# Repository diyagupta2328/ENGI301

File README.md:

# ENGI301
Repository for ENGI301 Coursework!

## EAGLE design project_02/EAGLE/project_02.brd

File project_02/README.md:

# Sign Talk PCB
This project is a PCB designed for Project 1 from this class. The updated system block diagram and a mechanical drawing is in a ppt in the project_02 folder. Through this project I was introduced to Eagle for designing and PCB and went through the process of getting a PCB ready for manufacture. 

This repository includes a schematic as a pdf, all the EAGLE files (library, schematic, board), manufacturing files, and implementation files.

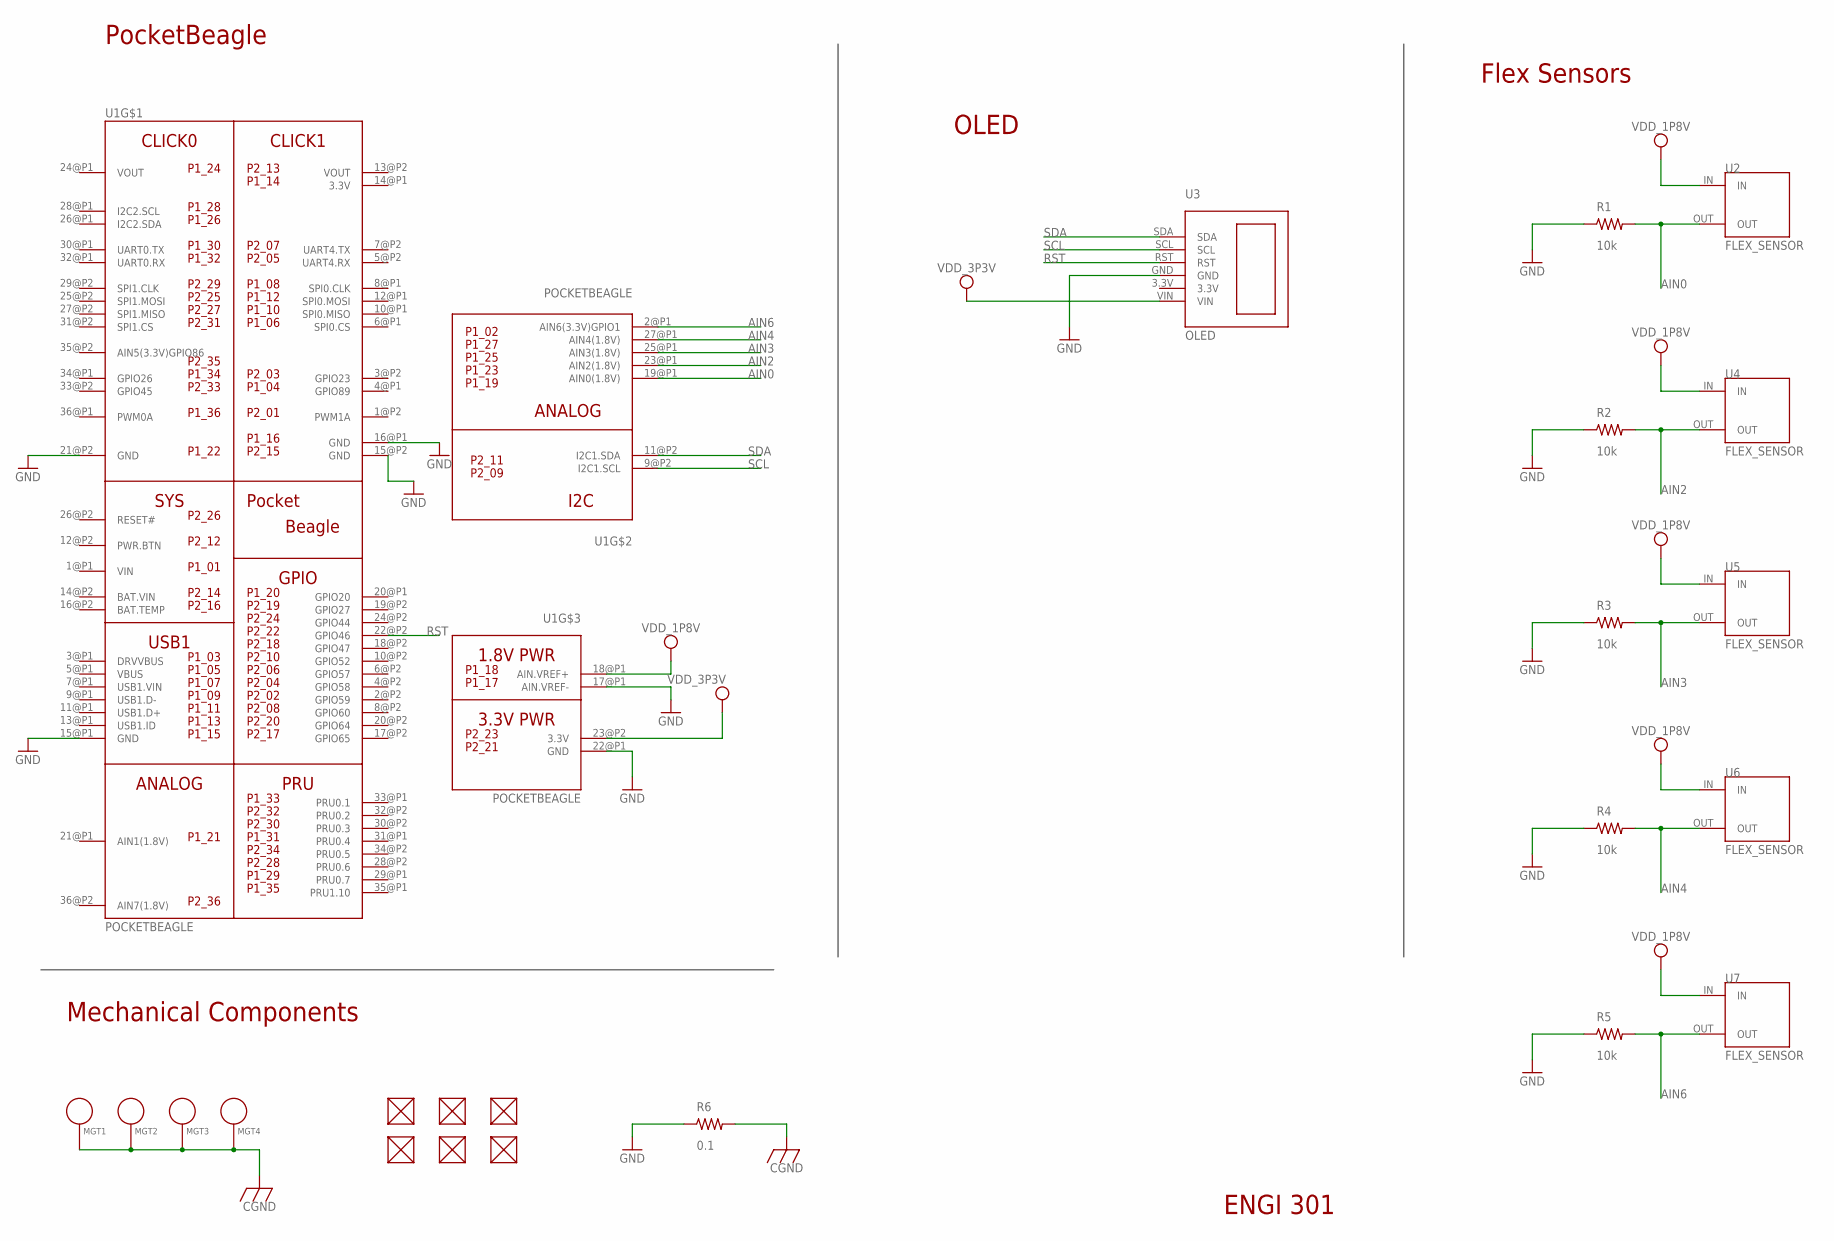
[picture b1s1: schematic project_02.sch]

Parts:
FUD1, FUD2, FUD3, FUD4, FUD5, FUD6: FIDUCIAL; FIDUCIAL_40MIL
MGT1, MGT2, MGT3, MGT4: MOUNTING_HOLE
R1, R2, R3, R4, R5: 10k; R0603
R6: 0.1; R0603
U1: POCKETBEAGLE
U2, U4, U5, U6, U7: FLEX_SENSOR
U3: OLED

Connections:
3.3V: U1.14@P1 (3.3V)
AIN0: R1.2, U1.19@P1 (AIN0(1.8V)), U2.OUT
AIN2: R2.2, U1.23@P1 (AIN2(1.8V)), U4.OUT
AIN3: R3.2, U1.25@P1 (AIN3(1.8V)), U5.OUT
AIN4: R4.2, U1.27@P1 (AIN4(1.8V)), U6.OUT
AIN6: R5.2, U1.2@P1 (AIN6(3.3V)GPIO1), U7.OUT
BAT.VIN: U1.14@P2 (BAT.VIN)
CGND: MGT1.P$1, MGT2.P$1, MGT3.P$1, MGT4.P$1, R6.2
GND: R1.1, R2.1, R3.1, R4.1, R5.1, R6.1, U1.15@P1 (GND), U1.15@P2 (GND), U1.16@P1 (GND), U1.17@P1 (AIN.VREF-), U1.21@P2 (GND), U1.22@P1 (GND), U3.GND
RST: U1.22@P2 (GPIO46), U3.RST
SCL: U1.9@P2 (I2C1.SCL), U3.SCL
SDA: U1.11@P2 (I2C1.SDA), U3.SDA
VDD_1P8V: U1.18@P1 (AIN.VREF+), U2.IN, U4.IN, U5.IN, U6.IN, U7.IN
VDD_3P3V: U1.23@P2 (3.3V), U3.VIN
VIN: U1.1@P1 (VIN)
VOUT: U1.13@P2 (VOUT), U1.24@P1 (VOUT)

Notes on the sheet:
Mechanical Components
PocketBeagle
OLED
Flex Sensors
ENGI 301

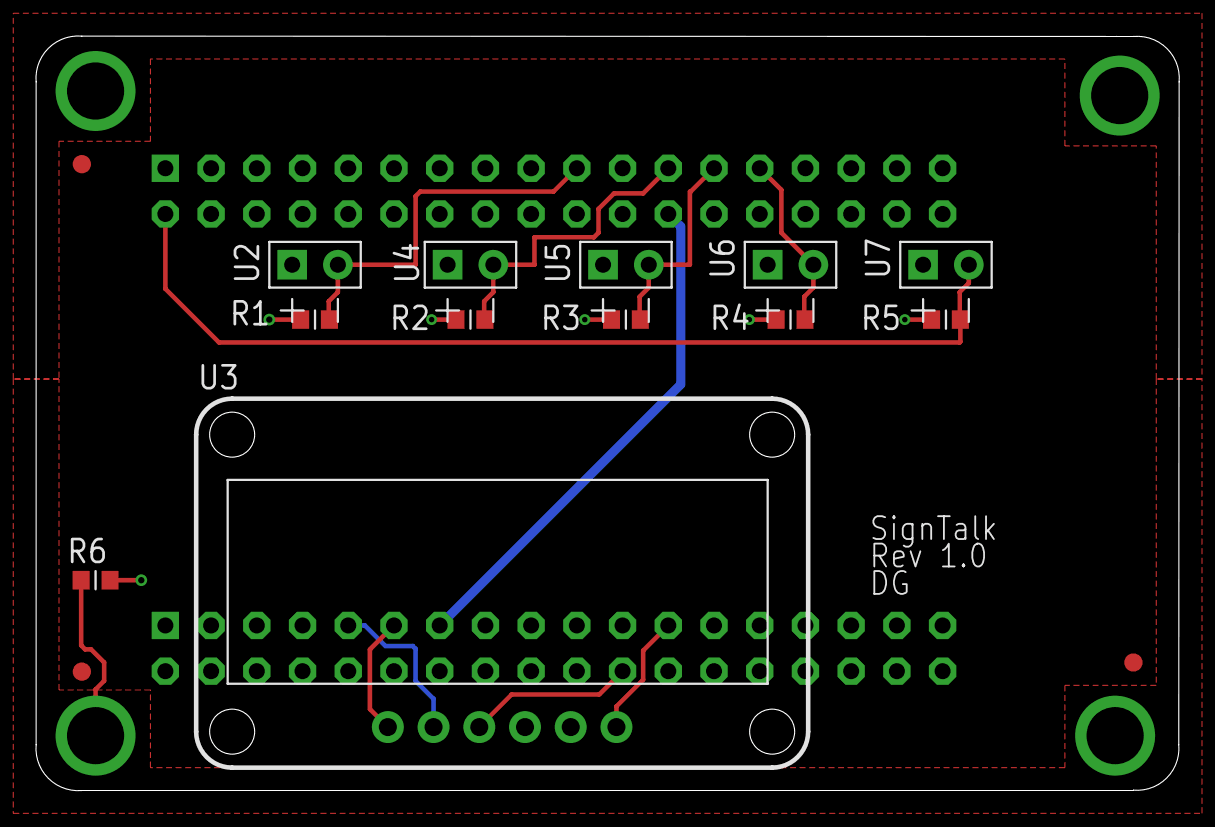
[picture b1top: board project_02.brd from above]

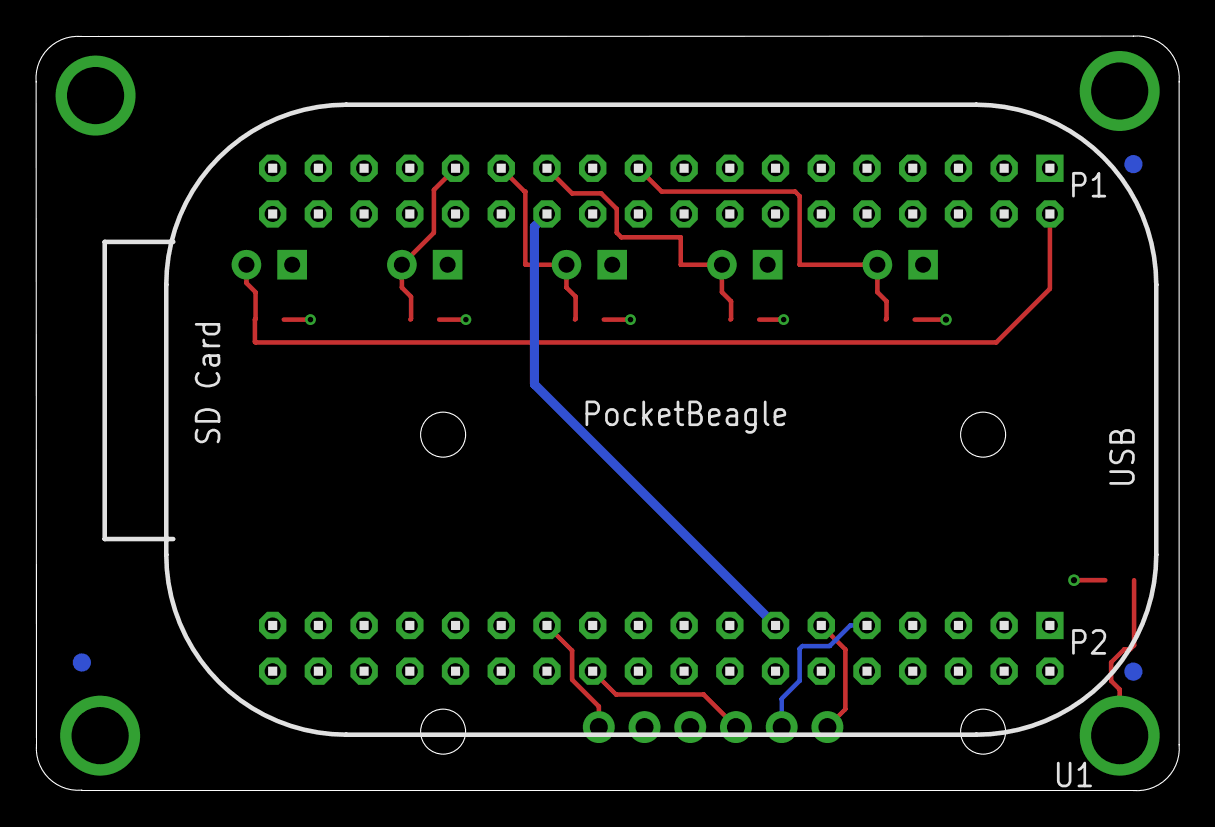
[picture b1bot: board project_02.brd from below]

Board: 4 copper layers, 63.5 x 41.9 mm, 23 parts (4 on the bottom side), 13 nets.

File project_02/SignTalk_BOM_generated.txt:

Partlist exported from C:/Users/dhira/OneDrive/Documents/EAGLE/project_02.sch at 12/15/2023 11:38 AM

Qty Value         Device        Package        Parts                              Description                                                                                                                                
1   0.1           R_R0603       R0603          R6                                 RESISTOR, American symbol                                                                                                                  
5   10k           R_R0603       R0603          R1, R2, R3, R4, R5                 RESISTOR, American symbol                                                                                                                                                                                                   
5   FLEX_SENSOR   FLEX_SENSOR   FLEX_SENSOR    U2, U4, U5, U6, U7                 This is the flex sensor device which consists of two header pins. The flex sensor can be connected via a jumper wire to these header pins. 
1   OLED          OLED          OLED           U3                                                                                                                                                                            
1   POCKETBEAGLE  POCKETBEAGLE  POCKETBEAGLE   U1

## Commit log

2023-11-14 Create HW 3
2023-11-14 Create HW 4
2023-12-11 Committing all files
